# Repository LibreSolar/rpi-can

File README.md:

# Libre Solar CAN interface for Raspberry Pi (Zero W)

**Caution:** Developed using nightly build of KiCAD because of several nice features. Unfortunately, the files are not compatible with the current stable version, but a new compatible stable release (v5) of KiCad is expected soon.

## CAN to Wifi Gateway

This interface PCB allows to read data from the CAN bus connecting the Libre Solar components. So the Raspberry Pi can be used as a gateway to IoT applications and energy monitoring (e.g. using Open Energy Monitor).

The pin header is compatible with all Raspberry Pi models, but the size is especially suited for the Raspberry Pi Zero W.

## Features:
- CAN interface via SPI using MCP2515 controller and TJA1042T/3 transceiver
- Power supply of Raspberry Pi via bus connector (RJ45)
- CAN transceiver standby connected to GPIO 24 (low power consumption mode possible)
- LED on GPIO 22 for custom status information

## Installation

Make sure to install the latest Raspbian onto your Raspberry Pi and connecto to it via SSH.

In order to activate the MCP2515 CAN controller, add the following lines to the file */boot/config.txt*:

```
# MCP 2515 CAN controller
dtparam=spi=on
dtoverlay=mcp2515-can0,oscillator=8000000,interrupt=25
```

Other guides for CAN on Raspberry Pi still suggest to add a line *dtoverlay=spi-bcm2835-overlay*. This is not true anymore, as Raspbian loads the BCM2835 SPI driver automatically.

Bring the interface up with the following command (change bitrate according to your needs):

```
sudo ip link set can0 up type can bitrate 250000
```

Now you should be able to send some test messages with *cansend* or watch messages on the bus:

```
candump can0
```

If something went wrong, try the following command to get some information about the CAN interface:

```
ip -s -d link show can0
```

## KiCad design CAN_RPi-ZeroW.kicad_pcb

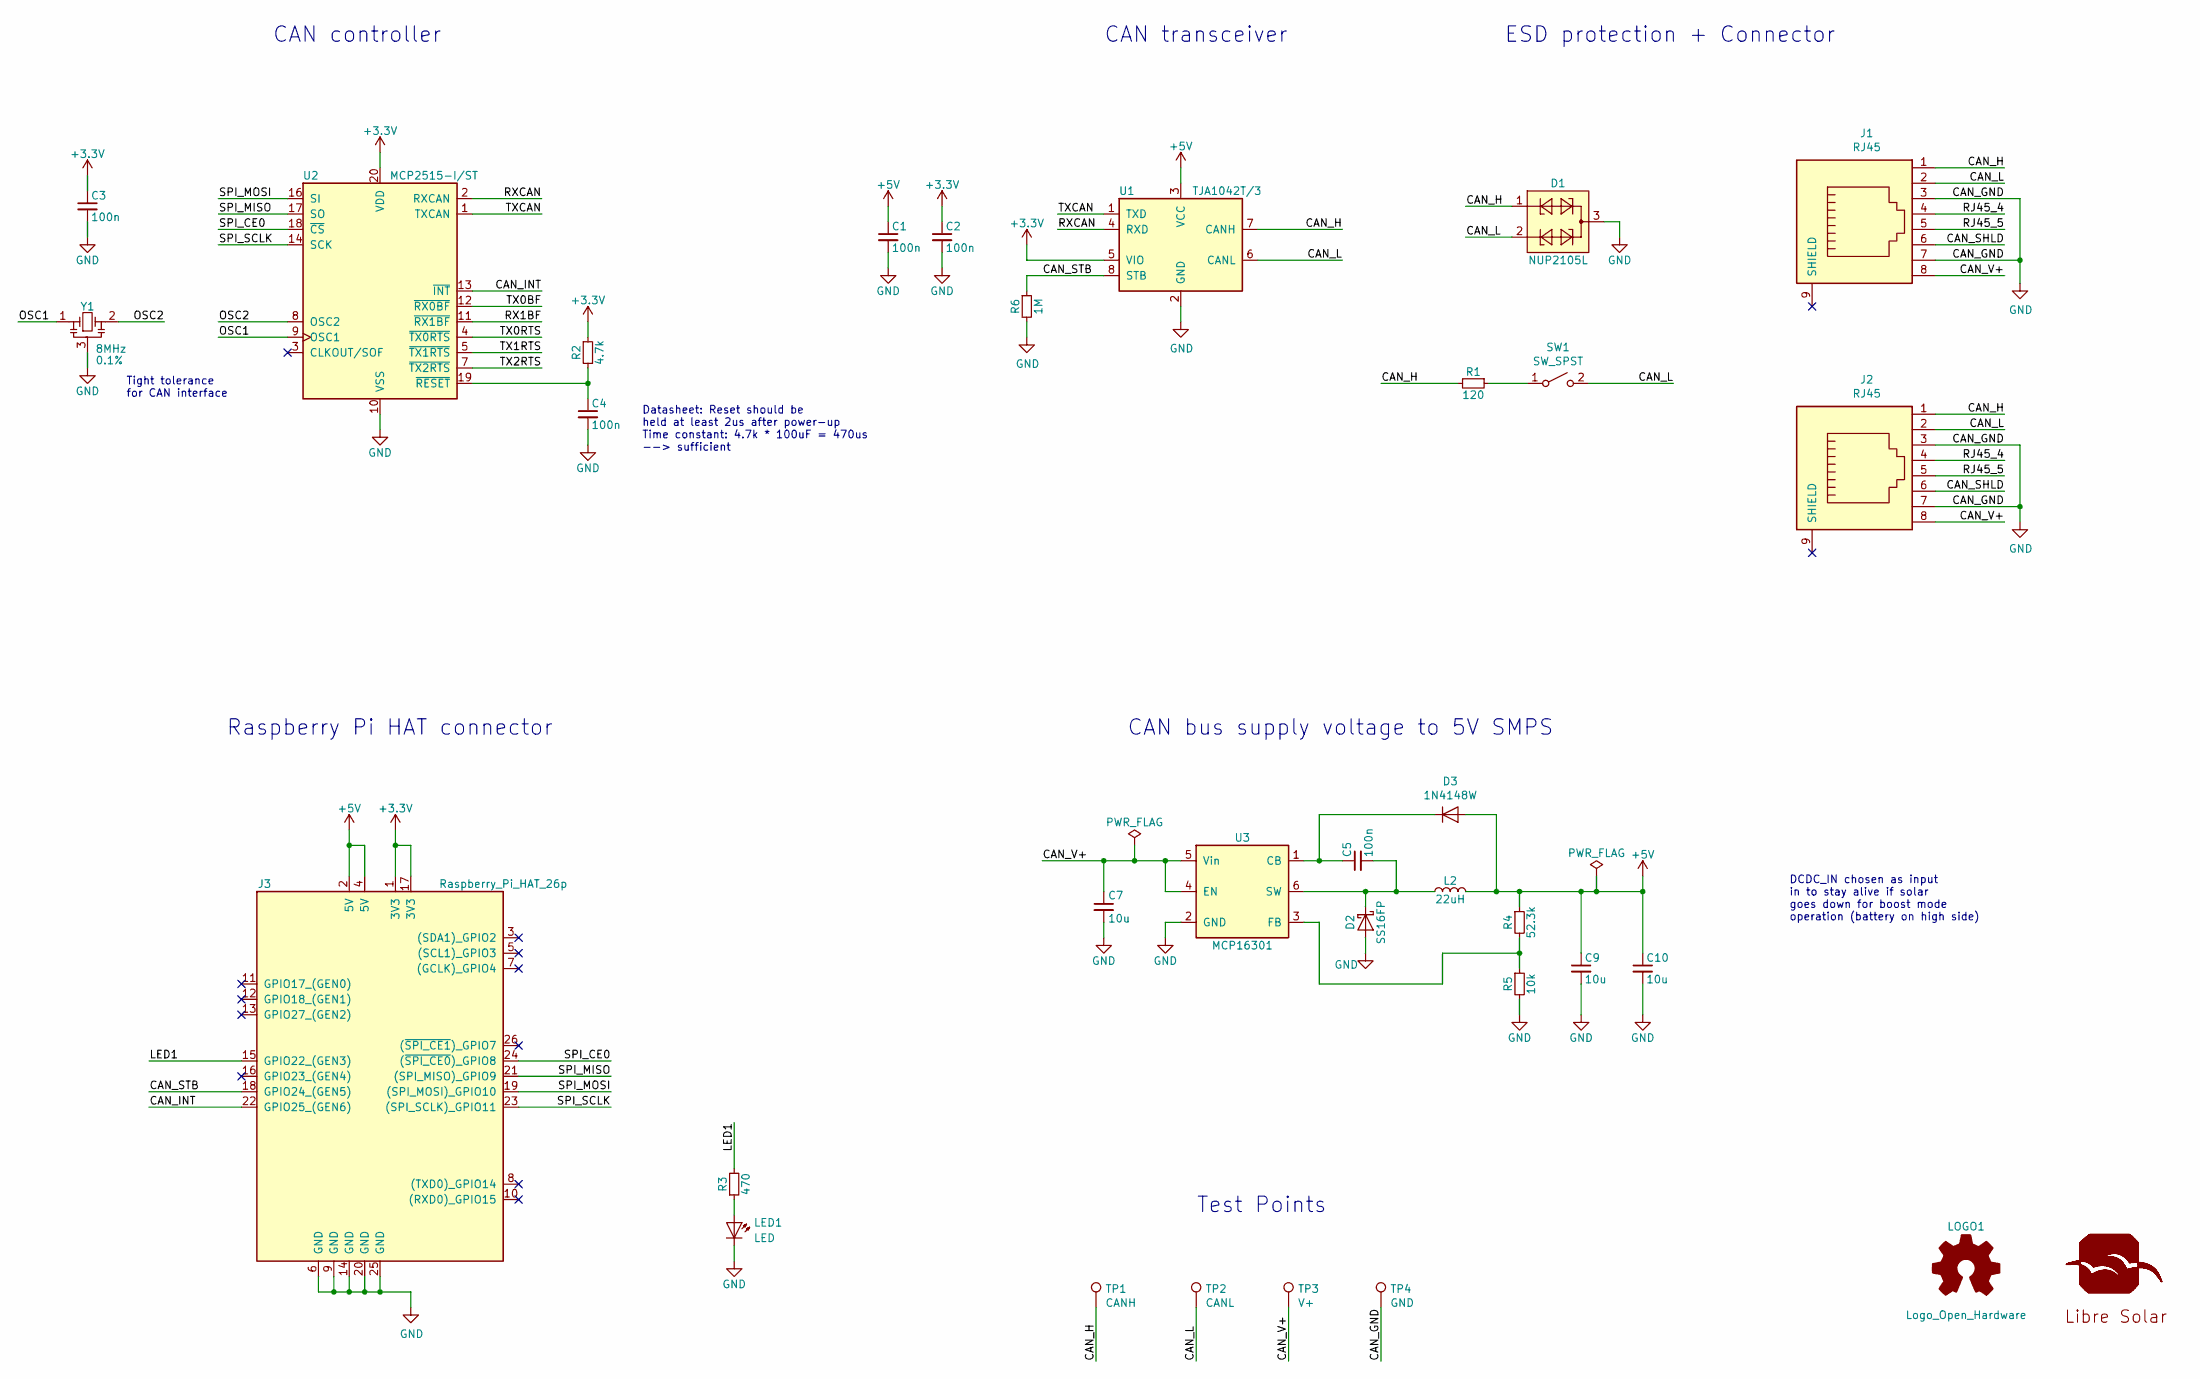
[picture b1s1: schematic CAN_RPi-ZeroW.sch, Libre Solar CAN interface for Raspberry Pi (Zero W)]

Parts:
C1, C2, C3, C4, C5: 100n; C_0603_1608; PartNumber GRM188R71H104KA93D
C7, C9, C10: 10u; C_0805_2012; PartNumber GRM21BR61E106KA73L
D1: NUP2105L; SOT-23; PartNumber NUP2105LT1G
D2: SS16FP; D_PowerDI-123; PartNumber SS16FP
D3: 1N4148W; D_SOD-123
J1, J2: RJ45; RJ45_8P8C
J3: Raspberry_Pi_HAT_26p; Socket_Strip_Straight_2x13_Pitch2.54mm
L2: 22uH; L_WE-TPC-4818; PartNumber SRR5028-470Y
LED1: LED; LED_0603
LOGO1: Logo_Open_Hardware; OSHW-Logo2_9.8x8mm_SilkScreen
N1: LIBRESOLAR_LOGO
R1: 120; R_1206_3216; PartNumber RC1206FR-07120RL
R2: 4.7k; R_0603_1608; PartNumber RC0603FR-074K7L
R3: 470; R_0603_1608; PartNumber RC0603FR-07470RL
R4: 52.3k; R_0603_1608; PartNumber RC0603FR-0752K3L
R5: 10k; R_0603_1608; PartNumber RC0603FR-0710KL
R6: 1M; R_0603_1608; PartNumber RC0603FR-071ML
SW1: SW_SPST; Pin_Header_Angled_1x02_Pitch2.54mm
TP1: CANH; Test_Point_Keystone_5000-5004_Miniature
TP2: CANL; Test_Point_Keystone_5000-5004_Miniature
TP3: V+; Test_Point_Keystone_5000-5004_Miniature
TP4: GND; Test_Point_Keystone_5000-5004_Miniature
U1: TJA1042T/3; SOIC-8_3.9x4.9mm_Pitch1.27mm
U2: MCP2515-I/ST; TSSOP-20_4.4x6.5mm_Pitch0.65mm
U3: MCP16301; SOT-23-6; PartNumber MCP16301
Y1: 8MHz; Resonator_Murata_CSTCE; Tolerance 0.1%; PartNumber CSTCE8M00G15C99-R0

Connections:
+3V3: C2.1, C3.1, J3.1 (3V3), J3.17 (3V3), R2.1, U1.5 (VIO), U2.20 (VDD)
+5V: C1.1, C9.1, C10.1, D3.2 (A), J3.2 (5V), J3.4 (5V), L2.2, R4.1, U1.3 (VCC)
/CAN_H: D1.1, J1.1, J2.1, R1.2, TP1.1, U1.7 (CANH)
/CAN_INT: J3.22 (GPIO25_(GEN6)), U2.13 (~INT)
/CAN_L: D1.2, J1.2, J2.2, SW1.2 (B), TP2.1, U1.6 (CANL)
/CAN_SHLD: J1.6, J2.6
/CAN_STB: J3.18 (GPIO24_(GEN5)), R6.1, U1.8 (STB)
/CAN_V+: C7.1, J1.8, J2.8, TP3.1, U3.4 (EN), U3.5 (Vin)
/LED1: J3.15 (GPIO22_(GEN3)), R3.2
/OSC1: U2.9 (OSC1), Y1.1
/OSC2: U2.8 (OSC2), Y1.2
/RJ45_4: J1.4, J2.4
/RJ45_5: J1.5, J2.5
/RX1BF: U2.11 (~RX1BF)
/RXCAN: U1.4 (RXD), U2.2 (RXCAN)
/SPI_CE0: J3.24 ((~SPI_CE0~)_GPIO8), U2.18 (~CS)
/SPI_MISO: J3.21 ((SPI_MISO)_GPIO9), U2.17 (SO)
/SPI_MOSI: J3.19 ((SPI_MOSI)_GPIO10), U2.16 (SI)
/SPI_SCLK: J3.23 ((SPI_SCLK)_GPIO11), U2.14 (SCK)
/TX0BF: U2.12 (~RX0BF)
/TX0RTS: U2.4 (~TX0RTS)
/TX1RTS: U2.5 (~TX1RTS)
/TX2RTS: U2.7 (~TX2RTS)
/TXCAN: U1.1 (TXD), U2.1 (TXCAN)
GND: C1.2, C2.2, C3.2, C4.2, C7.2, C9.2, C10.2, D1.3, D2.2 (A), J1.3, J1.7, J2.3, J2.7, J3.6 (GND), J3.9 (GND), J3.14 (GND), J3.20 (GND), J3.25 (GND), LED1.1 (K), R5.2, R6.2, TP4.1, U1.2 (GND), U2.10 (VSS), U3.2 (GND), Y1.3
unnamed: C4.1, R2.2, U2.19 (~RESET)
unnamed: C5.1, D3.1 (K), U3.1 (CB)
unnamed: C5.2, D2.1 (K), L2.1, U3.6 (SW)
unnamed: LED1.2 (A), R3.1
unnamed: R1.1, SW1.1 (A)
unnamed: R4.2, R5.1, U3.3 (FB)

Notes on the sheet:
Tight tolerance for CAN interface
CAN bus supply voltage to 5V SMPS
DCDC_IN chosen as input in to stay alive if solar goes down for boost mode operation (battery on high side)
Datasheet: Reset should be held at least 2us after power-up Time constant: 4.7k * 100uF = 470us --> sufficient
Raspberry Pi HAT connector
Test Points
CAN controller
CAN transceiver
ESD protection + Connector

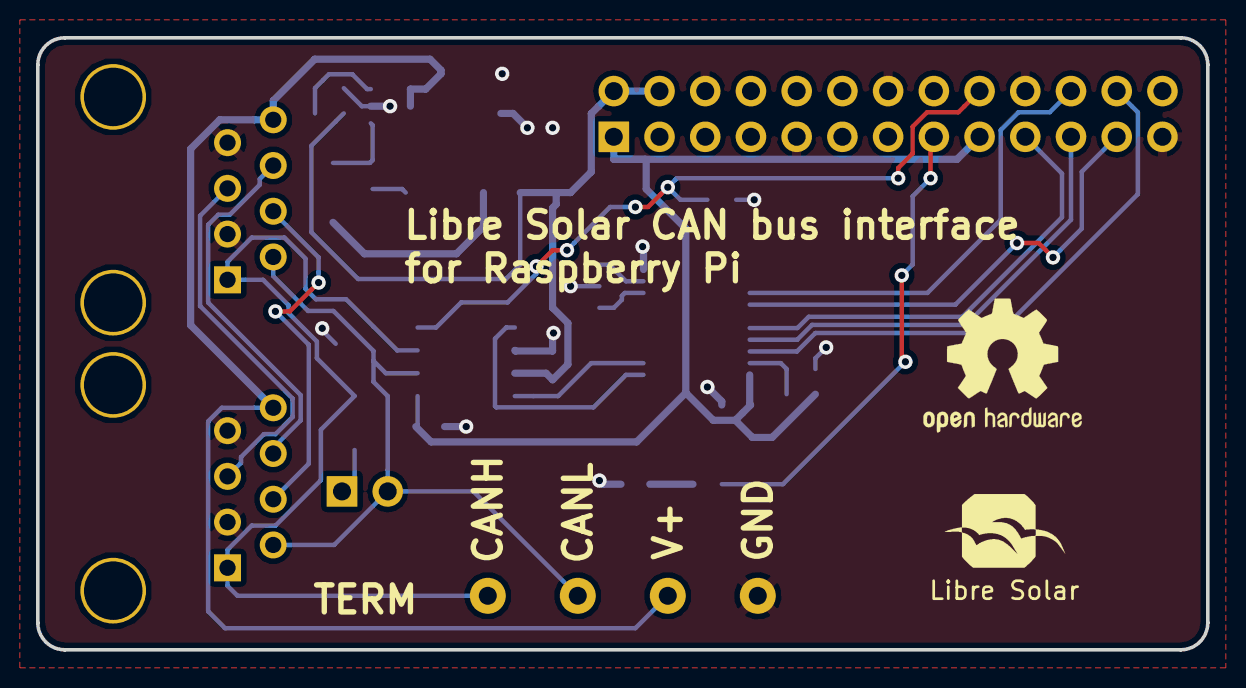
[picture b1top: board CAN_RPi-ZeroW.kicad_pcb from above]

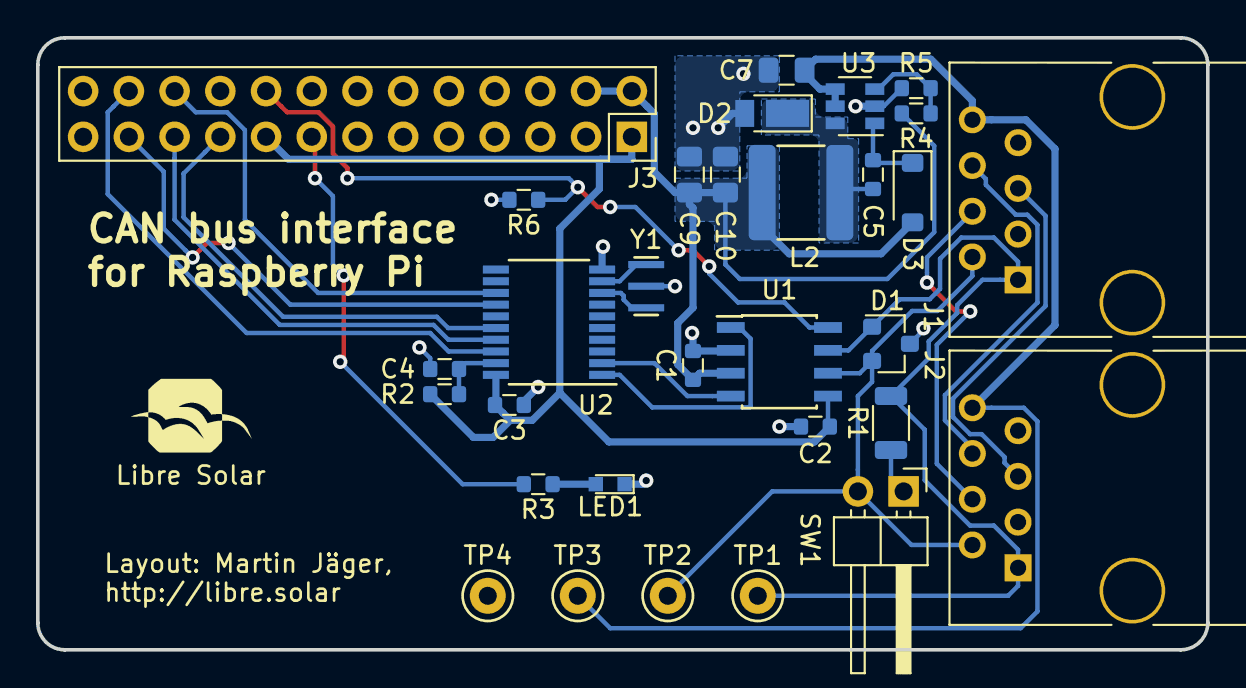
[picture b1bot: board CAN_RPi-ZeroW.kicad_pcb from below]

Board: 2 copper layers, 65.0 x 34.0 mm, 34 parts (32 on the bottom side), 26 nets.

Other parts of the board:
N1#2: LIBRESOLAR_LOGO

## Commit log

2017-12-19 PCB errors corrected and short installation guide added to README.md
    Corrected errors:
    - Pin header instead of socket strip used --> wrong pin layout of Raspi connector
    - STB pin of transceiver not connected --> sending of messages was not possible
    Now, small 26 pin connector is used instead of full 40 pin RPi HAT connector.
2017-12-19 Pull-down resistor for transceiver STB pin added.
